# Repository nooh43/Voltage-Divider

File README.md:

# Voltage-Divider
This voltage divider converts a 9V dc voltage to 5V.
# Equation applied
Vin*(Rx/Rt)=Vout\
9*( (200+300) / (100+200+300+300) ) = 5V

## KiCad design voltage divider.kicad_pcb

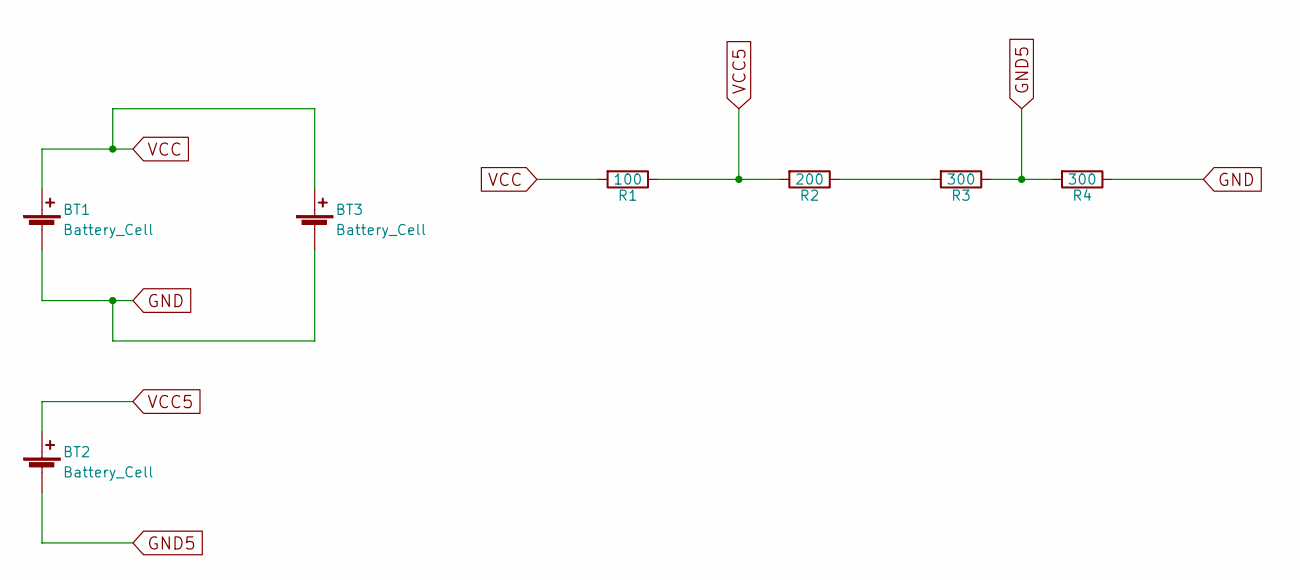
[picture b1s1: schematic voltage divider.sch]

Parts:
BT1, BT2, BT3: Battery_Cell; Socket_Strip_Straight_1x02_Pitch2.54mm
R1: 100; R_0805_HandSoldering
R2: 200; R_0805_HandSoldering
R3, R4: 300; R_0805_HandSoldering

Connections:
GND: BT1.2 (-), BT3.2 (-), R4.1
GND5: BT2.2 (-), R3.1, R4.2
unnamed: R2.1, R3.2
VCC: BT1.1 (+), BT3.1 (+), R1.2
VCC5: BT2.1 (+), R1.1, R2.2

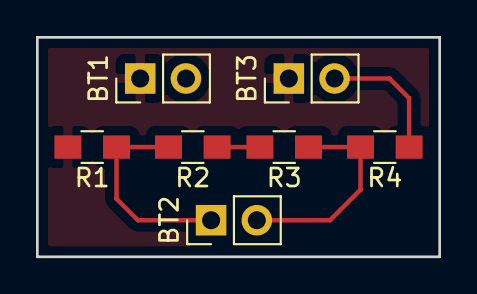
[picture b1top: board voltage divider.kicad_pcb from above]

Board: 2 copper layers, 22.4 x 12.2 mm, 7 parts (0 on the bottom side), 5 nets.
